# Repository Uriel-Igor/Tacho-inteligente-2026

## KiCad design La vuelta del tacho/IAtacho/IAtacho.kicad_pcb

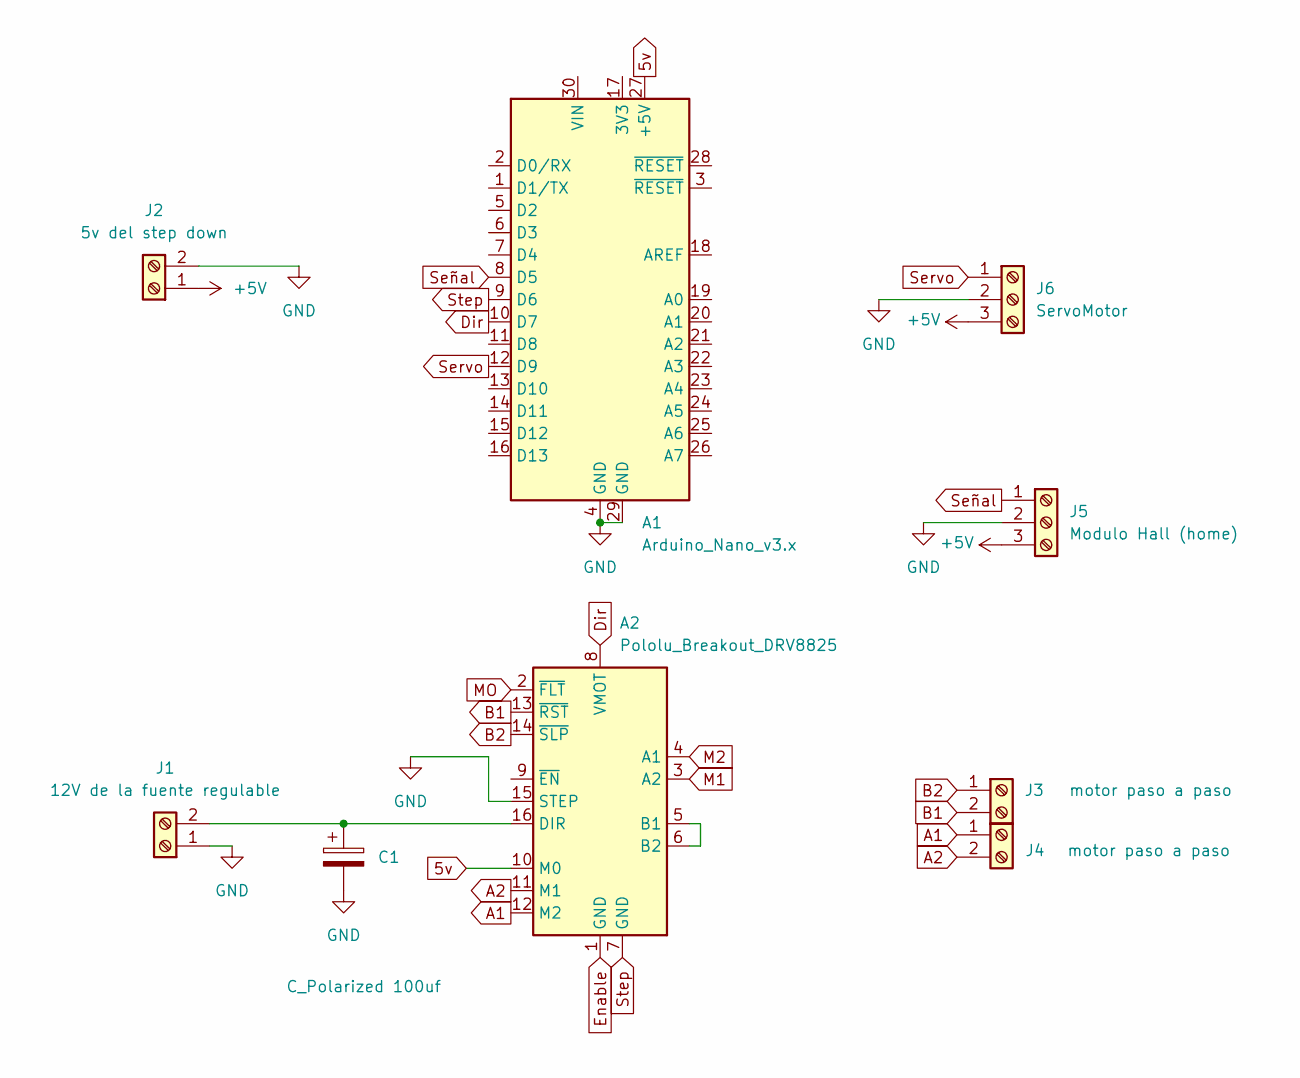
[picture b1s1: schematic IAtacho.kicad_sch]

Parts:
A1: Arduino_Nano_v3.x; Arduino_Nano
A2: Pololu_Breakout_DRV8825; Pololu_Breakout-16_15.2x20.3mm
C1: C_Polarized 100uf; CP_Radial_D6.3mm_P2.50mm
J1: 12V de la fuente regulable; TerminalBlock_MaiXu_MX126-5.0-02P_1x02_P5.00mm
J2: 5v del step down; TerminalBlock_MaiXu_MX126-5.0-02P_1x02_P5.00mm
J3, J4: motor paso a paso; TerminalBlock_MaiXu_MX126-5.0-02P_1x02_P5.00mm
J5: Modulo Hall (home); TerminalBlock_MaiXu_MX126-5.0-03P_1x03_P5.00mm
J6: ServoMotor; TerminalBlock_MaiXu_MX126-5.0-03P_1x03_P5.00mm

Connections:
5v: A1.27 (+5V), A2.10 (M0)
+5V: J2.1, J5.3, J6.3
A1: A2.12 (M2), J4.1
A2: A2.11 (M1), J4.2
B1: A2.13 (~RST), J3.2
B2: A2.14 (~SLP), J3.1
Dir: A1.10 (D7), A2.8 (VMOT)
Enable: A2.1 (GND)
GND: A1.4 (GND), A1.29 (GND), A2.15 (STEP), C1.2, J1.1, J2.2, J5.2, J6.2
M1: A2.3 (A2)
M2: A2.4 (A1)
MO: A2.2 (~FLT)
unnamed: A2.5 (B1), A2.6 (B2)
unnamed: A2.16 (DIR), C1.1, J1.2
Servo: A1.12 (D9), J6.1
Señal: A1.8 (D5), J5.1
Step: A1.9 (D6), A2.7 (GND)

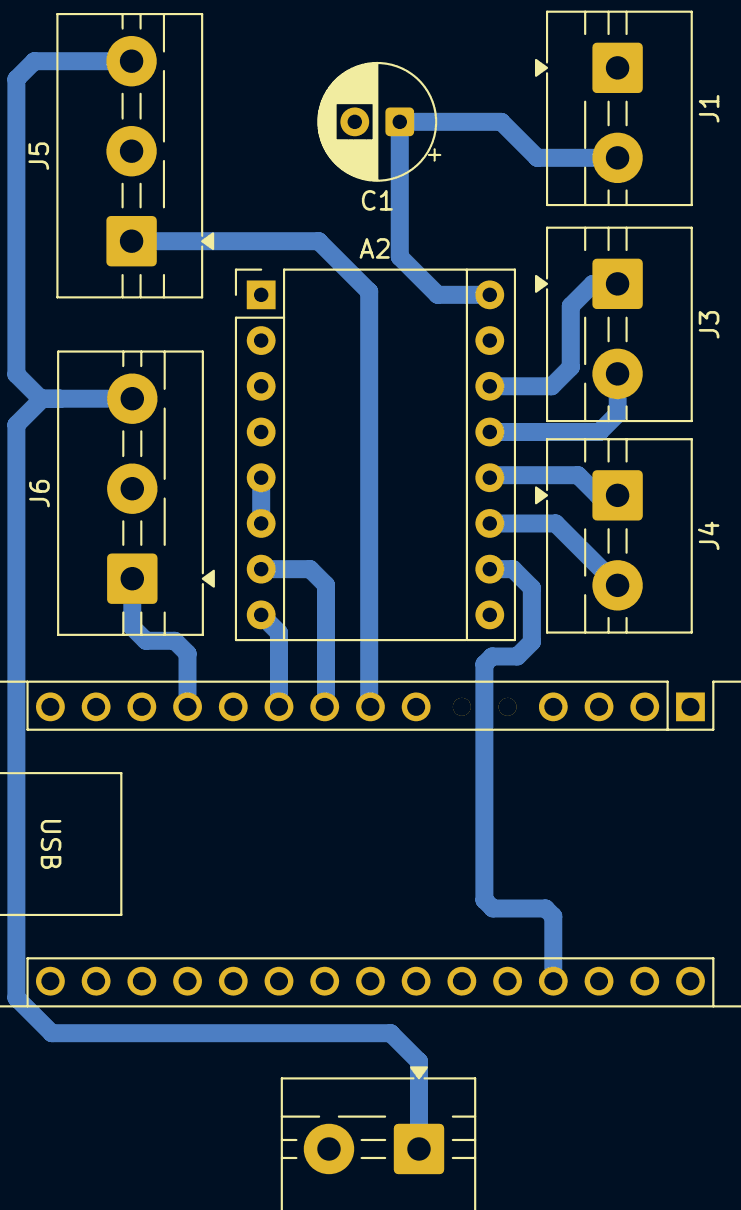
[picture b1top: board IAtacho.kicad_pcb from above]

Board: 2 copper layers, 9 parts (0 on the bottom side), 13 nets.

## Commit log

2026-05-25 PCB de tacho a correguir
2026-06-04 PCB arreglado sin 5v al arduino nano
